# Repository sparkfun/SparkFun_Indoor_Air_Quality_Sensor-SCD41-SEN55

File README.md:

SparkFun Indoor Air Quality Sensor - SCD41 SEN55 (Qwiic)
========================================

[*SparkFun Indoor Air Quality Sensor - SCD41 SEN55 (SEN-25200)*](https://www.sparkfun.com/products/25200)

The SparkFun Indoor Air Quality Sensor - SCD41 SEN55 (Qwiic) combines two excellent indoor air quality sensors in the SCD41 and SEN55 from Sensirion<sup>&trade;</sup> to provide a comprehensive indoor air quality sensor that measures CO<sub>2</sub>, Volatile Organic Compounds (VOCs), particulate matter (PM1.0, 2.5, 4, and 10) along with temperature and relative humidity. The board includes a pair of Qwiic connectors as well as a 0.1"-spaced through-hole header for I<sup>2</sup>C connections as well as power inputs.

Repository Contents
-------------------

* **/docs** - Markdown files for Hookup Guide
* **/Documents** - Datasheets, additional product information
* **/Firmware** - Example code 
* **/Hardware** - Eagle design files (.brd, .sch)

Documentation
--------------
* **[SparkFun SCD4x Library](https://github.com/sparkfun/SparkFun_SCD4x_Arduino_Library)** - Arduino library for SDC4x sensor boards.
* **[Sensirion Arduino Core Library](https://github.com/Sensirion/arduino-core)** - Arduino core library for Sensirion sensors.
* **[Sensirion SEN5x Library](https://github.com/Sensirion/arduino-i2c-sen5x)** - Arduino library for the Sensirion SEN55.
* **[Hookup Guide](https://sparkfun.github.io/SparkFun_Indoor_Air_Quality_Sensor-SCD41-SEN55)** - Basic hookup guide for the SparkFun Indoor Air Quality Sensor - SCD41 SEN55 (Qwiic).

Product Versions
----------------
* [SEN-25200](https://www.sparkfun.com/products/25200) - Initial product release.

License Information
-------------------

This product is _**open source**_! 

Please review the LICENSE.md file for license information. 

If you have any questions or concerns on licensing, please contact technical support on our [SparkFun forums](https://forum.sparkfun.com/viewforum.php?f=152).

Distributed as-is; no warranty is given.

- Your friends at SparkFun.

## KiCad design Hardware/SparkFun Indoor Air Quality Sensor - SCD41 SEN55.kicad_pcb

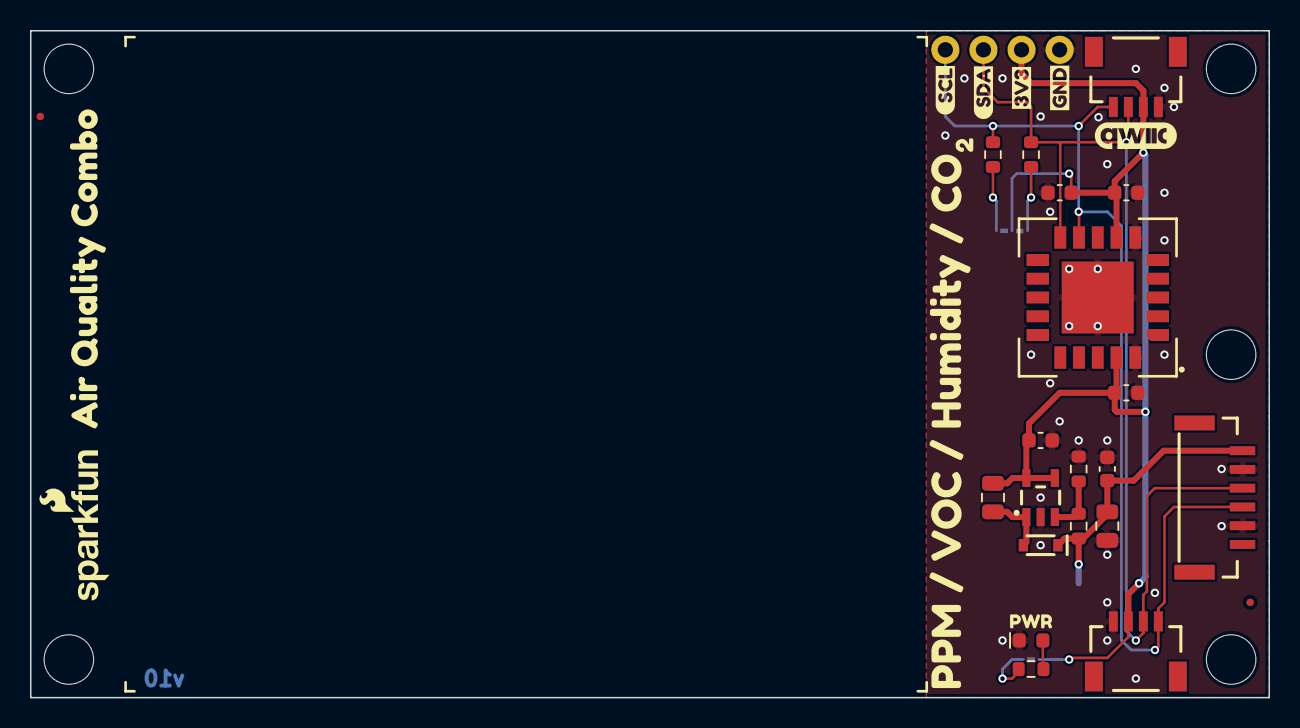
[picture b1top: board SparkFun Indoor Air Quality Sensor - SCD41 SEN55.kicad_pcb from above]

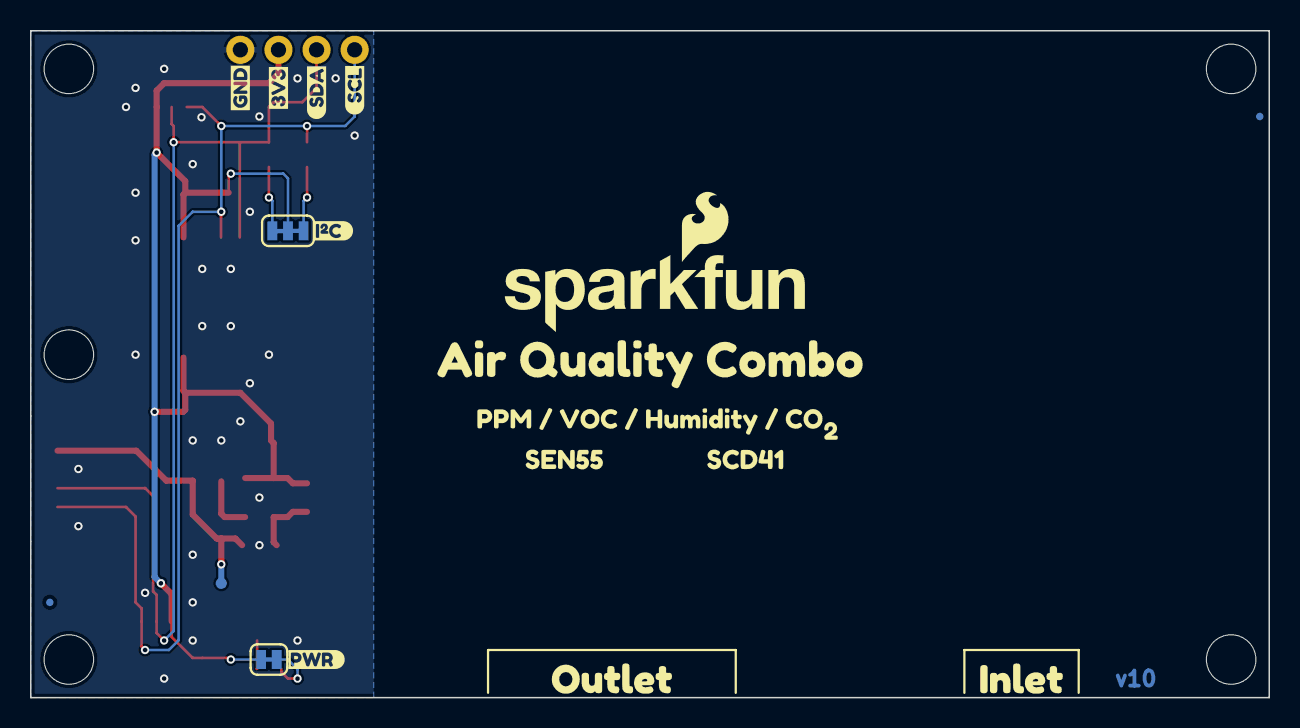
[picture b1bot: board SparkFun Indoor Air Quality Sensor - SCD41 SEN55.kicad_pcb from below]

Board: 2 copper layers, 82.5 x 44.5 mm, 55 parts (18 on the bottom side), 11 nets.

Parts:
C1, C5: 0.1uF; C_0603_1608Metric
C2: 22uF; C_0805_2012Metric
C4: 4.7uF; C_0603_1608Metric
C7, C9: 1.0uF; C_0603_1608Metric
D1: Red; LED_0603_1608Metric_Red
D2: PMEG4005EJ; SOD-323
FID1, FID2, FID3, FID4: Fiducial_0.5mm; Fiducial_0.5mm_Mask1mm
G4: OSHW_Logo; Creative_Commons_License
J1, J2: Qwiic_RA; JST_SMD_1.0mm-4_RA
J3: Conn_01x04; 1x04
JP1: Jumper_2_NC_Trace
JP2: Jumper_3_NC-2_Trace
L2: 10uH; C_0805_2012Metric
R1, R2: 2.2k; R_0603_1608Metric
R3: 4.7k; R_0603_1608Metric
R5: 100k; R_0603_1608Metric
R6: 33k; R_0603_1608Metric
ST1, ST2, ST3, ST4, ST5: Standoff
TP1: 0.75mm; TestPoint-0.75mm
U3: SCD41; SCD4x
U4: SEN55_Outline; SEN5x_Outline
U5: AP3012; SOT23-5
U6: SEN55_Connector; JST_SMD_1.25mm-6_Locking
kibuzzard-65A8A6F0: G***; kibuzzard-65A8A6F0
kibuzzard-65A8A8B4: G***; kibuzzard-65A8A8B4
kibuzzard-65A8A70D: G***; kibuzzard-65A8A70D
kibuzzard-65A8A702: G***; kibuzzard-65A8A702
kibuzzard-65A8A717: G***; kibuzzard-65A8A717
kibuzzard-65A8AE5A: G***; kibuzzard-65A8AE5A
kibuzzard-65A8AE51: G***; kibuzzard-65A8AE51
kibuzzard-65A8AE62: G***; kibuzzard-65A8AE62
kibuzzard-65A8AEA5: G***; kibuzzard-65A8AEA5
kibuzzard-65A8AED7: G***; kibuzzard-65A8AED7
kibuzzard-65A8AFF1: G***; kibuzzard-65A8AFF1
kibuzzard-65A8AFFA: G***; kibuzzard-65A8AFFA
kibuzzard-65A8B05B: G***; kibuzzard-65A8B05B
kibuzzard-65A8B028: G***; kibuzzard-65A8B028
kibuzzard-65A8B037: G***; kibuzzard-65A8B037
kibuzzard-65A75D7A, kibuzzard-65A75D7A#2: G***; kibuzzard-65A75D7A
kibuzzard-65A7583B: G***; kibuzzard-65A7583B
kibuzzard-65A75820: G***; kibuzzard-65A75820
kibuzzard-65CFEE26: G***; kibuzzard-65CFEE26
kibuzzard-65F20621: G***; kibuzzard-65F20621

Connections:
3.3V: C1.1, C4.1, C5.1, C7.1, J1.2, J2.2, J3.2, JP1.2 (B), JP2.2 (C), L2.1, U3.7 (VDD), U3.19 (VDDH), U5.4 (~SHDN), U5.5 (IN)
5V: C2.1, C9.1, D2.C, R5.1, TP1.1, U6.1 (VDD)
GND: C1.2, C2.2, C4.2, C5.2, C7.2, C9.2, D1.1 (K), J1.1, J2.1, J3.1, R6.2, U3.6 (GND), U3.20 (GND), U3.21 (GND), U5.2 (GND), U6.2 (GND), U6.5 (SEL)
unnamed: D1.2 (A), R3.2
unnamed: JP1.1 (A), R3.1
unnamed: JP2.1 (A), R2.1
unnamed: JP2.3 (B), R1.1
unnamed: R5.2, R6.1, U5.3 (FB)
unnamed: D2.A, L2.2, U5.1 (SW)
SCL: J1.4, J2.4, J3.4, R2.2, U3.9 (SCL), U6.4 (SCL)
SDA: J1.3, J2.3, J3.3, R1.2, U3.10 (SDA), U6.3 (SDA)

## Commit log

2024-02-16 Move connector to avoid cable over silk
2024-02-16 Add first firmware examples
2024-02-20 Remove proto files
2024-02-20 Add schematic. Fix ignore.
2024-03-06 Pre design review changes
2024-03-06 Pre design review updates
2024-03-06 Initial docs commit
    Adding docs folder with template files & other mkdocs/GH pages files.
2024-03-13 Add PTH at 0.8"
2024-03-13 Add panel files
2024-03-13 File rename
2024-03-19 Docs review
    Final documentation review updates. Removing embedded code snippets prior to release to allow the page to build. Will re-add once repo is public.
2024-03-21 Docs Update
    Updated docs files with final product name edits & added content for hardware overview and software sections.
2024-08-05 Fix PROD_ID on SEN55 connector and module.
2024-08-14 Update examples
2024-08-22 Docs update
    Adding photo assets & updating relevant sections for photos. Other minor tweaks & file additions.
2024-08-23 Update 3D models
2024-08-27 Docs review update
2024-08-28 Adding workflows/mkdocs.yml
    Adding workflows folder & mkdocs.yml for page building.
2024-09-19 Introduction update
    Adding product showcase video, feature photo & other minor fixes.
2024-10-01 Update software_setup.md
    Fixed formatting error for library download buttons.
2024-10-01 Deployed bbd2fbe with MkDocs version: 1.6.1
2024-10-25 Deployed 2ec7cb6 with MkDocs version: 1.6.1
2024-10-25 Update mkdocs.yml
    Analytics update.

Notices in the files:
parts and their libraries:
Released under the Creative Commons Attribution Share-Alike 4.0 License
https://creativecommons.org/licenses/by-sa/4.0
